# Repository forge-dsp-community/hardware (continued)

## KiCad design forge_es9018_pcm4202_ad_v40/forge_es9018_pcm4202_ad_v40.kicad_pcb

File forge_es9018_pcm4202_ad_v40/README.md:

# Forge ES9018/PCM4202 AD/DA V4.0 – KiCad-Rekonstruktion

> **Unfertiger Zwischenstand, nicht poliert.** Die Rekonstruktion stammt aus 300-dpi-Bildern und ist nicht gegen eine echte Platine geprüft. Es fehlen noch 6 Verbindungen, viele Bauteilwerte sind unbekannt, die Bauteilnamen sind neu vergeben und der DRC meldet Kosmetik (Details unten). Nicht zum Fertigen verwenden.

| Unterseite (Bauteile) | Oberseite |
|---|---|
|  |  |

3D-Renderings aus KiCad (`kicad-cli pcb render --rotate '-35,0,±30' --zoom 0.9 --background opaque`).

Quelle: `forge/pcbs/ad_da/eln_ad_da/V40` (bitbucket.org/forge-dsp/pcbs, Mark Duprau,
Lizenz CC BY-NC-SA 4.0). Diese Rekonstruktion steht unter derselben Lizenz.

Das ist die **zentrale AD/DA-Trägerplatine** der Forge DSP 96ELN / ETON CORED8 (V40):
3× PCM4202 (ADC), 1× ES9018 (8-Kanal-DAC), PCA9554 (I²C-Expander). Die analogen
I/V-Ausgangsplatinen (`output/eln/V30`, `output/eln-3/…`) werden in die 4 Steckplätze
J1–J4 gesteckt, die Eingangsplatinen in die 6 Schlitze an der Oberkante.

## Dateien

| Datei | Inhalt |
|---|---|
| `forge_es9018_pcm4202_ad_v40.kicad_pro/.kicad_sch/.kicad_pcb` | KiCad-10-Projekt |
| `forge_ad_da.kicad_sym` | Projekt-Symbole (PCM4202, ES9018, PCA9554, generische) |
| `forge_ad_da.pretty/` | 48 Footprints, Padgeometrie aus den Originaldaten vermessen |
| `rekonstruktion/` | Python-Skripte + `model.json` (Bauteile, Pads, Netze) |

## Ausgangsdaten

Im Repo gibt es **keine echten Gerber/Eagle-Dateien**, nur:

* Eagle-Renderings je Lage (`TOP`, `ROUTE2`, `ROUTE3`, `BOTTOM`, `PADS`, `VIAS`, `HOLES`, `TPLACE`, `BPLACE`, `MILLING`), 300 dpi
* `ES9018-PCM4202_AD.pdf` von Eurocircuits: 4er-Nutzen, Kupferlagen als 300-dpi-Bilder aus den echten Gerbern, Bohrplan mit Bohrtabelle
* das Schaltplanbild `…-SCHEMA.png` (Bus-Darstellung, Netznamen am Bus nicht sichtbar)

## Vorgehen

1. Die Eurocircuits-Bilder werden per Kreuzkorrelation auf die Eagle-Renderings registriert (gedreht um 90°, ±1 px).
2. Kupfer zählt nur dort, wo **beide** Quellen Kupfer zeigen (Eagle um 1 px aufgeweitet). Jede Quelle hat bei 300 dpi eigene 1-px-Brücken; die UND-Verknüpfung entfernt sie.
3. Netze ergeben sich aus den Kupfer-Inseln pro Lage, verbunden über Vias und Durchsteckpads.
4. Pads kommen aus den Lötstopp-Öffnungen (PCB-View Top/Bottom); die ICs werden über Pinraster plus Netzplausibilität eingepasst.
5. Konsistenzprüfung gegen den Original-Schaltplan (`validate.py`, `cmp.py`). Bestätigt sind z. B.:
   * PCM4202: S/M→3V3, FMT0/1→GND, FS0/FS1/HPFD/MCLK/LRCLK/BCLK gemeinsam, SDOUT je Chip getrennt
   * PCA9554 IO0…IO5 = CLIPL.3, CLIPR.3, CLIPL.2, CLIPR.2, CLIPL.1, CLIPR.1, IO6 = nRST.PCM4202, IO7 = RST.ES9018 (genau wie im Original)
   * J1…J4: I.2+, I.2−VREF, I.2−, I.1+, I.1−VREF, I.1− = VOUT2/1 … VOUT8/7 des ES9018
   * X100 Pin 3…16 wie im Original (SDA/SCL.PIPE, AD.OUT.1…3, LOCK, MCLK, BCLK.IN/OUT, LRCLK)
6. Die Bohrungen stimmen 1:1 mit der Eurocircuits-Bohrtabelle überein: Vias 0,25/0,30/0,40/0,50/0,60/0,80 mm, 20× 0,7 mm Halbloch-Kontakte, 4× 1,0 mm, 3× 2,0 mm.

## Ergebnis

* **Platine:** 53,21 × 56,39 mm, 4 Lagen. Umriss mit Schlitzen aus der Fräslage.
  Kupfer auf F/In1/In2/B als **3759 Leiterbahn-Segmente** und **174 Flächen-Zonen** mit Netz (siehe „Kupfer: Leiterbahnen statt Zonen“), dazu 332 Vias, 3 Montagebohrungen und der Bestückungsdruck oben/unten als Grafik.
  Fast alle Bauteile sitzen auf der **Unterseite**.
* **Schaltplan:** 97 Symbole, 103 Netze, Bauteilgruppen verdrahtet, globale Labels nur zwischen Gruppen (siehe Schaltplan). Schaltplan und Platine sind verknüpft; der DRC mit Schaltplan-Abgleich ist fehlerfrei.
* **DRC** (`kicad-cli pcb drc --refill-zones --schematic-parity`): 0 Kurzschlüsse, 0 Clearance-Fehler, **6 offene Verbindungen** (siehe unten), genau wie in der Zonen-Fassung. Der Rest ist kosmetisch und war vorher schon da: 67 × Kupfer am Halbloch-/Platinenrand (Pads und Vias des Randkontakts), 13 Courtyard-Überlappungen, 1 THT-Pad im Courtyard, Druck über Kupfer.
  Neu sind nur Warnungen:
  * 69 × „Leiterbahn mit offenem Ende“, überwiegend Sackgassen im Originalkupfer.
  * 9 × „Via nur einlagig angebunden“: Diese Vias haben auf den übrigen Lagen nur ihren eigenen Ring als Kupfer (~1 mm). Als Zone zählte dieser Ring für KiCad als Verbindung, als Via-Pad nicht mehr; elektrisch ändert sich nichts.

### Kupfer: Leiterbahnen statt Zonen

Kupfer liegt als **Leiterbahnen** vor. Breite Flächen (im Original Eagle-Polygone, auch Via-Felder) sind **Zonen mit Netz**, die KiCad selbst füllt (Clearance 0,08 mm, Thermals an THT-Pads).

Erzeugt mit `rekonstruktion/tracks.py` aus `polys.json`:

* Jede Kupferinsel wird mit 25 px/mm gerastert. Flächen werden über den Distanz-Transform erkannt (morphologisches Öffnen), der Rest wird skelettiert (Zhang-Suen), in Pfade zwischen End- und Knotenpunkten zerlegt, mit Douglas-Peucker vereinfacht, kurze Sporne fallen weg.
* Spurbreite = 2 × Distanz-Transform (Median), abgerundet auf Eagle-Breiten (0,1524 … 1,016 mm) und zusätzlich so begrenzt, dass Clearance zu fremdem Kupfer und Randabstand passen. Über das eigene Kupfer hinaus darf eine Spur höchstens bis zur Hälfte der Lücke zum Nachbarn ragen.
* Endpunkte an Pads/Vias desselben Netzes rasten auf die Pad-/Via-Mitte ein, an Flächen werden sie 0,3 mm hinein verlängert.
* Fläche wird, was einschließlich Pads und Vias ≥ 1,2 mm breit ist, dazu angrenzendes Kupfer ab 0,9 mm Breite. Danach rastert das Skript die erzeugten Spuren und vergleicht sie mit dem Originalkupfer (Formprüfung): Bleibt ein dicker Bereich (≥ 0,3 mm dick, ≥ 0,15 mm²) unbedeckt, wird er mit 0,5 mm Umgebung zur Fläche und die Insel neu berechnet. So werden Via-Felder Flächen statt Haufen kurzer breiter Spuren.
* Die Montagelöcher H1–H3 sind voll an die Flächen angebunden (ohne Thermal): In den Ecken erreicht die Fläche sie nur von einer Seite, mit Thermal bliebe nur ein Steg.
* Die Bild-Pads sind oft größer als die Footprint-Pads, manche Vias liegen direkt am Pad. Was nach dem Skelett innerhalb einer Insel noch getrennt ist, verbindet das Skript deshalb über einen kürzesten Weg durch das Originalkupfer.
* Zum Schluss prüft das Skript mit dem KiCad-DRC und macht Spuren mit Clearance- oder Randfehlern schrittweise schmaler. Spuren, die schon 0,1 mm breit sind, schiebt es um das fehlende Stück vom Hindernis weg.
* Die frühere Zonen-Fassung liegt als `rekonstruktion/forge_es9018_pcm4202_ad_v40_zonen.kicad_pcb` bei. Neu erzeugen mit `/usr/bin/python3 rekonstruktion/tracks.py .`; das Skript liest immer die Zonen-Fassung.

### Offene Punkte (im Original vorhanden, im 300-dpi-Bild zu dünn)

In KiCad erscheinen sie als Luftlinie und müssen von Hand nachgezogen werden:
`AD.OUT.3`, `nRST.PCM4202`, `VINR+.1`, `VINR+.2`, `VINR+.3`, `VOUT4+`.

### Teile, die nicht im Original-Schaltplanbild stehen

| Ref | Gehäuse | Funktion (aus Netzen abgeleitet) |
|---|---|---|
| U201 | SOT-23-5 | LDO 5V0 → **1V2_AVCC** (VDD_L/R des ES9018), Eingang über C254 (Ferrit/R?) |
| U202 | SOT-89 | Regler 3V3.NOHF → **1V2_DVCC** (VDD1–3 des ES9018) |
| U203 | SOIC-8 | Regler für **3V3_AVCC_L / 3V3_AVCC_R** (Eingang von X102.3) |
| U204 | SOT-23 | unbekannt (X102.4, C251/C252/C247) |
| X102 | 1×04, 2,54 mm | Versorgungseingang der Analogregler |
| X101 | 1×04, 2,0 mm | DATA2…DATA5 des ES9018 (Datenkanäle) |

### Unsicherheiten

* **Referenzen:** Der Original-Bestückungsdruck hat keine Namen. IC101…IC105, R10/C35 usw. folgen dem Schaltplan, alle passiven Teile heißen neu **C2xx/R2xx**, Pads ohne erkennbares Bauteil **TPxx**.
* **Werte:** Werte stammen aus dem Original-Schaltplan, zugeordnet über die Funktion (VREF/VCC/VDD-Tantal 47 µF, Abblock 100 nF, Eingang 2,7 nF). Mit `?` markierte Werte sind unbekannt; aus den Bildern lässt sich nicht unterscheiden, ob ein Pad-Paar R, C oder Ferrit ist.
* **Eingangsschlitze (Oberkante):** Bei C207…C212, C259 und TP1…TP4 ist unklar, ob es Kondensatoren oder Lötkontakte der Eingangsplatinen sind. Die 100-pF-Kondensatoren aus dem Schaltplan sitzen vermutlich auf den Eingangsplatinen.
* **Bauteilanzahl:** 71 Footprints mit Pads (ohne Randkontakt, Steckplätze, Jumper, Padgruppen). Ein Teil davon ist auf realen Platinen wohl unbestückt; der V40e-Schaltplan markiert mehrere Kondensatoren als „n.c.“.
* **U.FL (X-MCLK-DA):** Nur der Signalpad (TP17, Netz `MCLK.DA` → ES9018 XI) ist sicher erkannt. Die Massepads liegen in der GND-Fläche.

## 3D-Modelle

* Alle Bauteile haben KiCad-eigene 3D-Modelle (STEP aus `${KICAD10_3DMODEL_DIR}`), eingetragen in `forge_ad_da.pretty` und in der Platine. Fast alles sitzt auf der Unterseite; die Bilder oben zeigen beide Seiten.
* Zuordnung: C_0603 (Pad-Abstand bis 2 mm) → `C_0603_1608Metric` (R201 → `R_0603_1608Metric`), C_0805 → `C_0805_2012Metric`, L_C_1206ish → `C_1206_3216Metric`, Tantal Case C → `CP_EIA-6032-28_Kemet-C`, SSOP-28 (PCM4202) → `SSOP-28_5.3x10.2mm_P0.65mm`, TQFP-64 (ES9018) → `TQFP-64_10x10mm_P0.5mm`, HVQFN-16 (PCA9554) → `WQFN-16-1EP_3x3mm_P0.5mm_EP1.6x1.6mm`, SOIC-8 → `SOIC-8_3.9x4.9mm_P1.27mm`, SOT-23 → `SOT-23`, SOT-23-5 → `SOT-23-5`, SOT-89 → `SOT-89-3`, X101 → `PinHeader_1x04_P2.00mm_Vertical`, X102 → `PinHeader_1x04_P2.54mm_Vertical`.
* C210, C211, C253 und C259 haben 0603-Pads, aber 3,6…4,7 mm Pad-Abstand. Ihr Modell richtet sich nach dem Abstand, damit der Körper auf den Pads liegt: `C_1206_3216Metric` bzw. `C_1812_4532Metric` für C259. Die echte Bauform ist unbekannt.
* U201 (SOT-23-5) und U203 (SOIC-8): Die Pin-Reihenfolge der rekonstruierten Footprints ist gespiegelt. Die Gehäuse sitzen richtig auf den Pads, die Pin-1-Markierung des Modells liegt aber am anderen Ende der Pin-1-Reihe. U204 (`SOT-23-3_custom`) passt nur ungefähr auf die Pads.
* Ohne Modell, weil Kupfer bzw. Bohrung der Platine selbst: Randkontakt X100, Steckplätze J1…J4 für die I/V-Platinen, Lötbrücken JP1…JP3, Bohrungen H1…H3. Die Pad-Gruppen TP1…TP18 haben kein Modell, weil das Bauteil (falls bestückt) unbekannt ist.
* Bilder: `kicad-cli pcb render --side bottom` bzw. `--side top` nach dem Füllen der Zonen.
* Neu setzen nach jedem Neuerzeugen von Bibliothek oder Platine (`pcb.py`, `tracks.py`): `/usr/bin/python3 rekonstruktion/models3d.py .`. Das Skript trägt die Modelle in die Bibliothek, die Platine und `rekonstruktion/<name>_zonen.kicad_pcb` ein.

## Schaltplan

`rekonstruktion/sch_layout.py` ordnet den aus `sch.py` erzeugten Schaltplan neu an (A2):

* Je IC ein Block: Die Kondensatoren eines Pins hängen an einer Drahtbahn direkt am Pin, gestaffelt nach außen, damit sich nichts kreuzt. Kondensatoren zwischen zwei Pins (VIN+/VIN−) stehen senkrecht dazwischen. Abblockkondensatoren hängen am Versorgungspin, an dem sie auf der Platine am nächsten sitzen (seitliche Pins über eine Bahn, Pins oben/unten per Draht).
* Globale Labels gibt es nur für Netze zwischen Blöcken (Takte, I²C, CLIP/Reset, VOUT → J1…J4, Randkontakt). Versorgung erscheint als Power-Symbole.
* Verdrahtete Netze tragen ihren Namen als lokales Label (`/NAME`). Die Netznamen der Platine sind daran angeglichen (`sch_layout.py <projekt> --pcb`). Der DRC mit Schaltplan-Abgleich ist ohne Abweichung.
* Die Netzliste ist geprüft identisch mit der Label-Fassung (`rekonstruktion/<name>_labels.kicad_sch`). Die ERC zeigt nur noch die 15 Warnungen zu Ein-Pin-Netzen, die es vorher auch gab.

## Neu erzeugen

`rekonstruktion/run_all.sh`, dann `polys.py`, `pcb.py <ordner> <name>` und `sch.py <ordner> <name>`, danach `/usr/bin/python3 rekonstruktion/sch_layout.py .` (Schaltplan anordnen). Das ergibt die Zonen-Fassung.
Dann `rekonstruktion/forge_es9018_pcm4202_ad_v40_zonen.kicad_pcb` löschen und `/usr/bin/python3 rekonstruktion/tracks.py .` ausführen (sichert die neue Zonen-Fassung und erzeugt die Leiterbahnen).
Danach `kicad-cli pcb drc --refill-zones --save-board --schematic-parity` ausführen.
Die Skripte lesen ihre Pfade aus Umgebungsvariablen: `FORGE_PCBS` (Checkout von forge-dsp/pcbs), `REK_TOOLS` (Ordner mit den Extraktionsskripten), `SDIR` (Arbeitsordner für Zwischenstände).

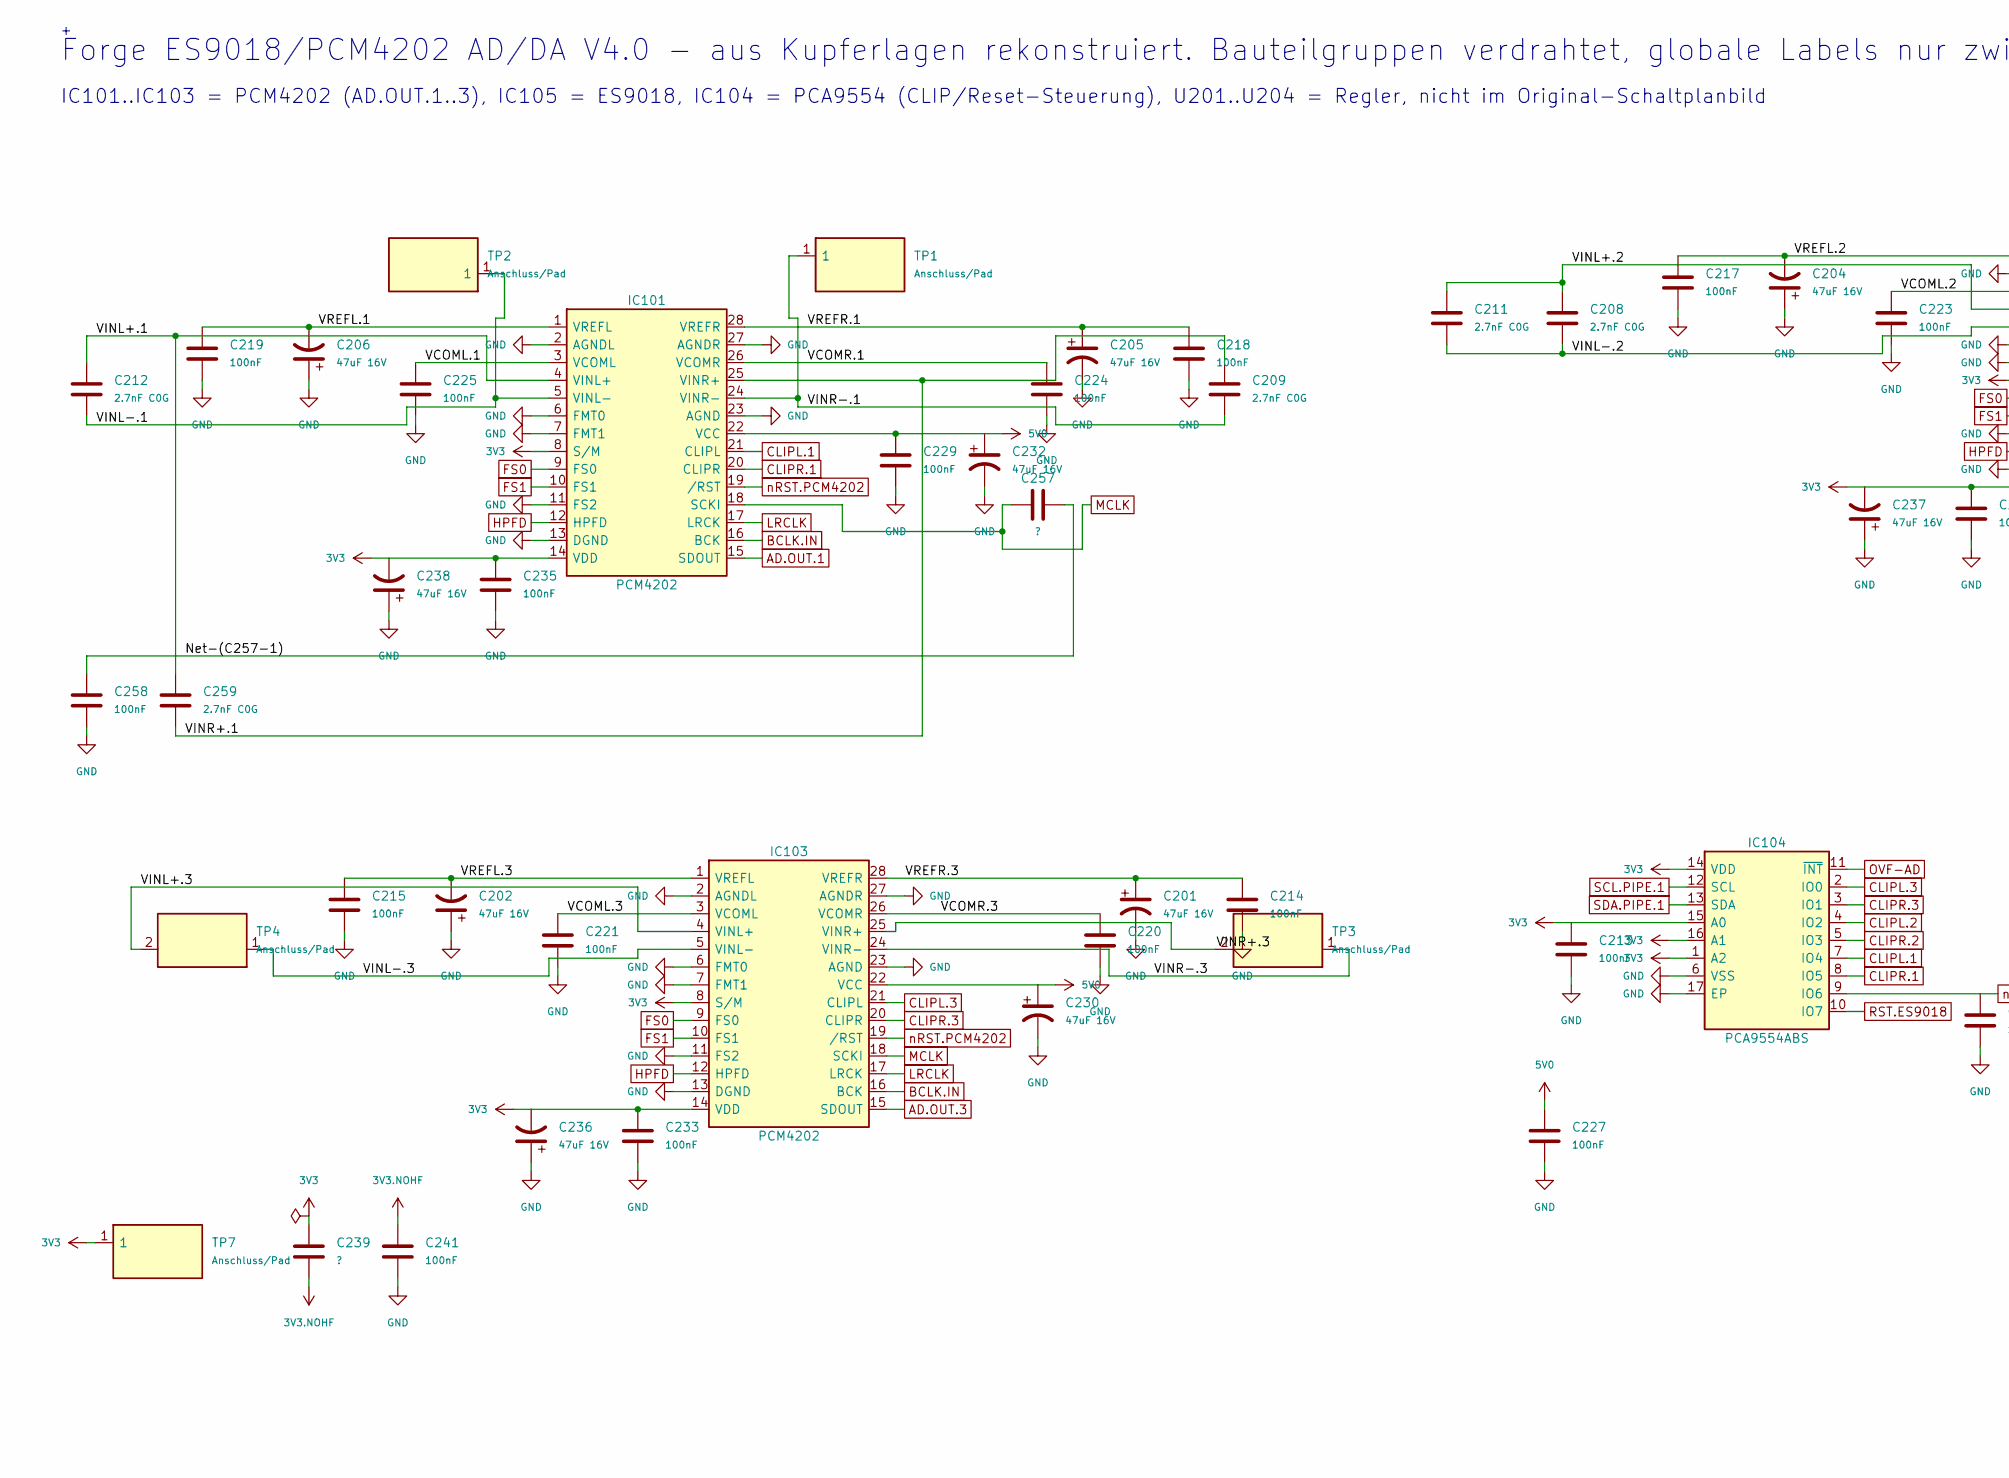
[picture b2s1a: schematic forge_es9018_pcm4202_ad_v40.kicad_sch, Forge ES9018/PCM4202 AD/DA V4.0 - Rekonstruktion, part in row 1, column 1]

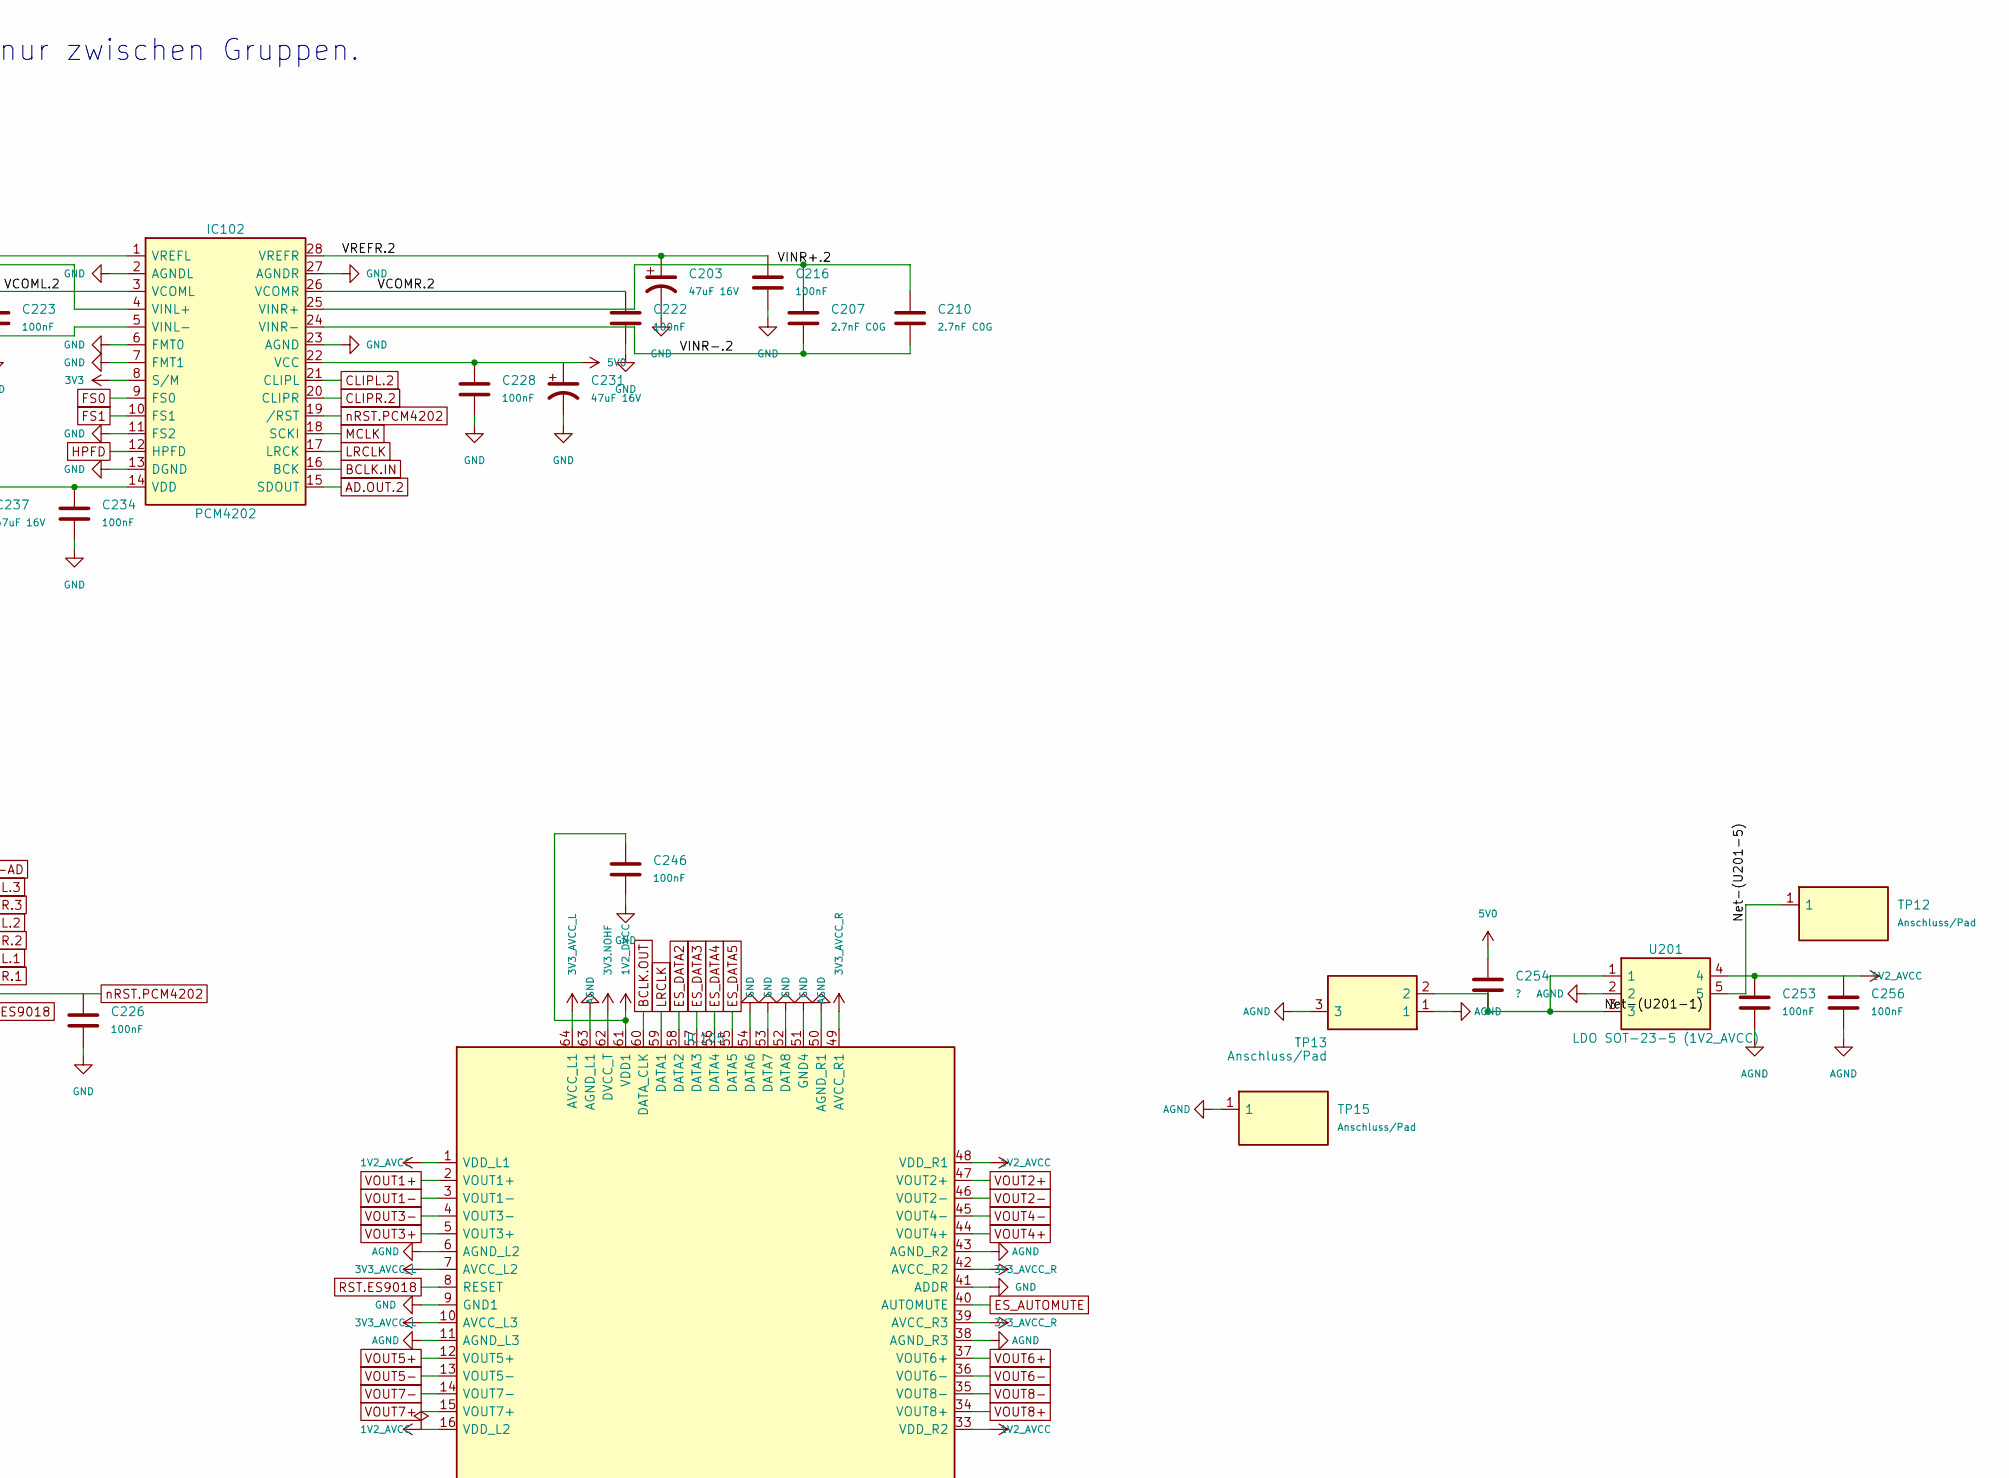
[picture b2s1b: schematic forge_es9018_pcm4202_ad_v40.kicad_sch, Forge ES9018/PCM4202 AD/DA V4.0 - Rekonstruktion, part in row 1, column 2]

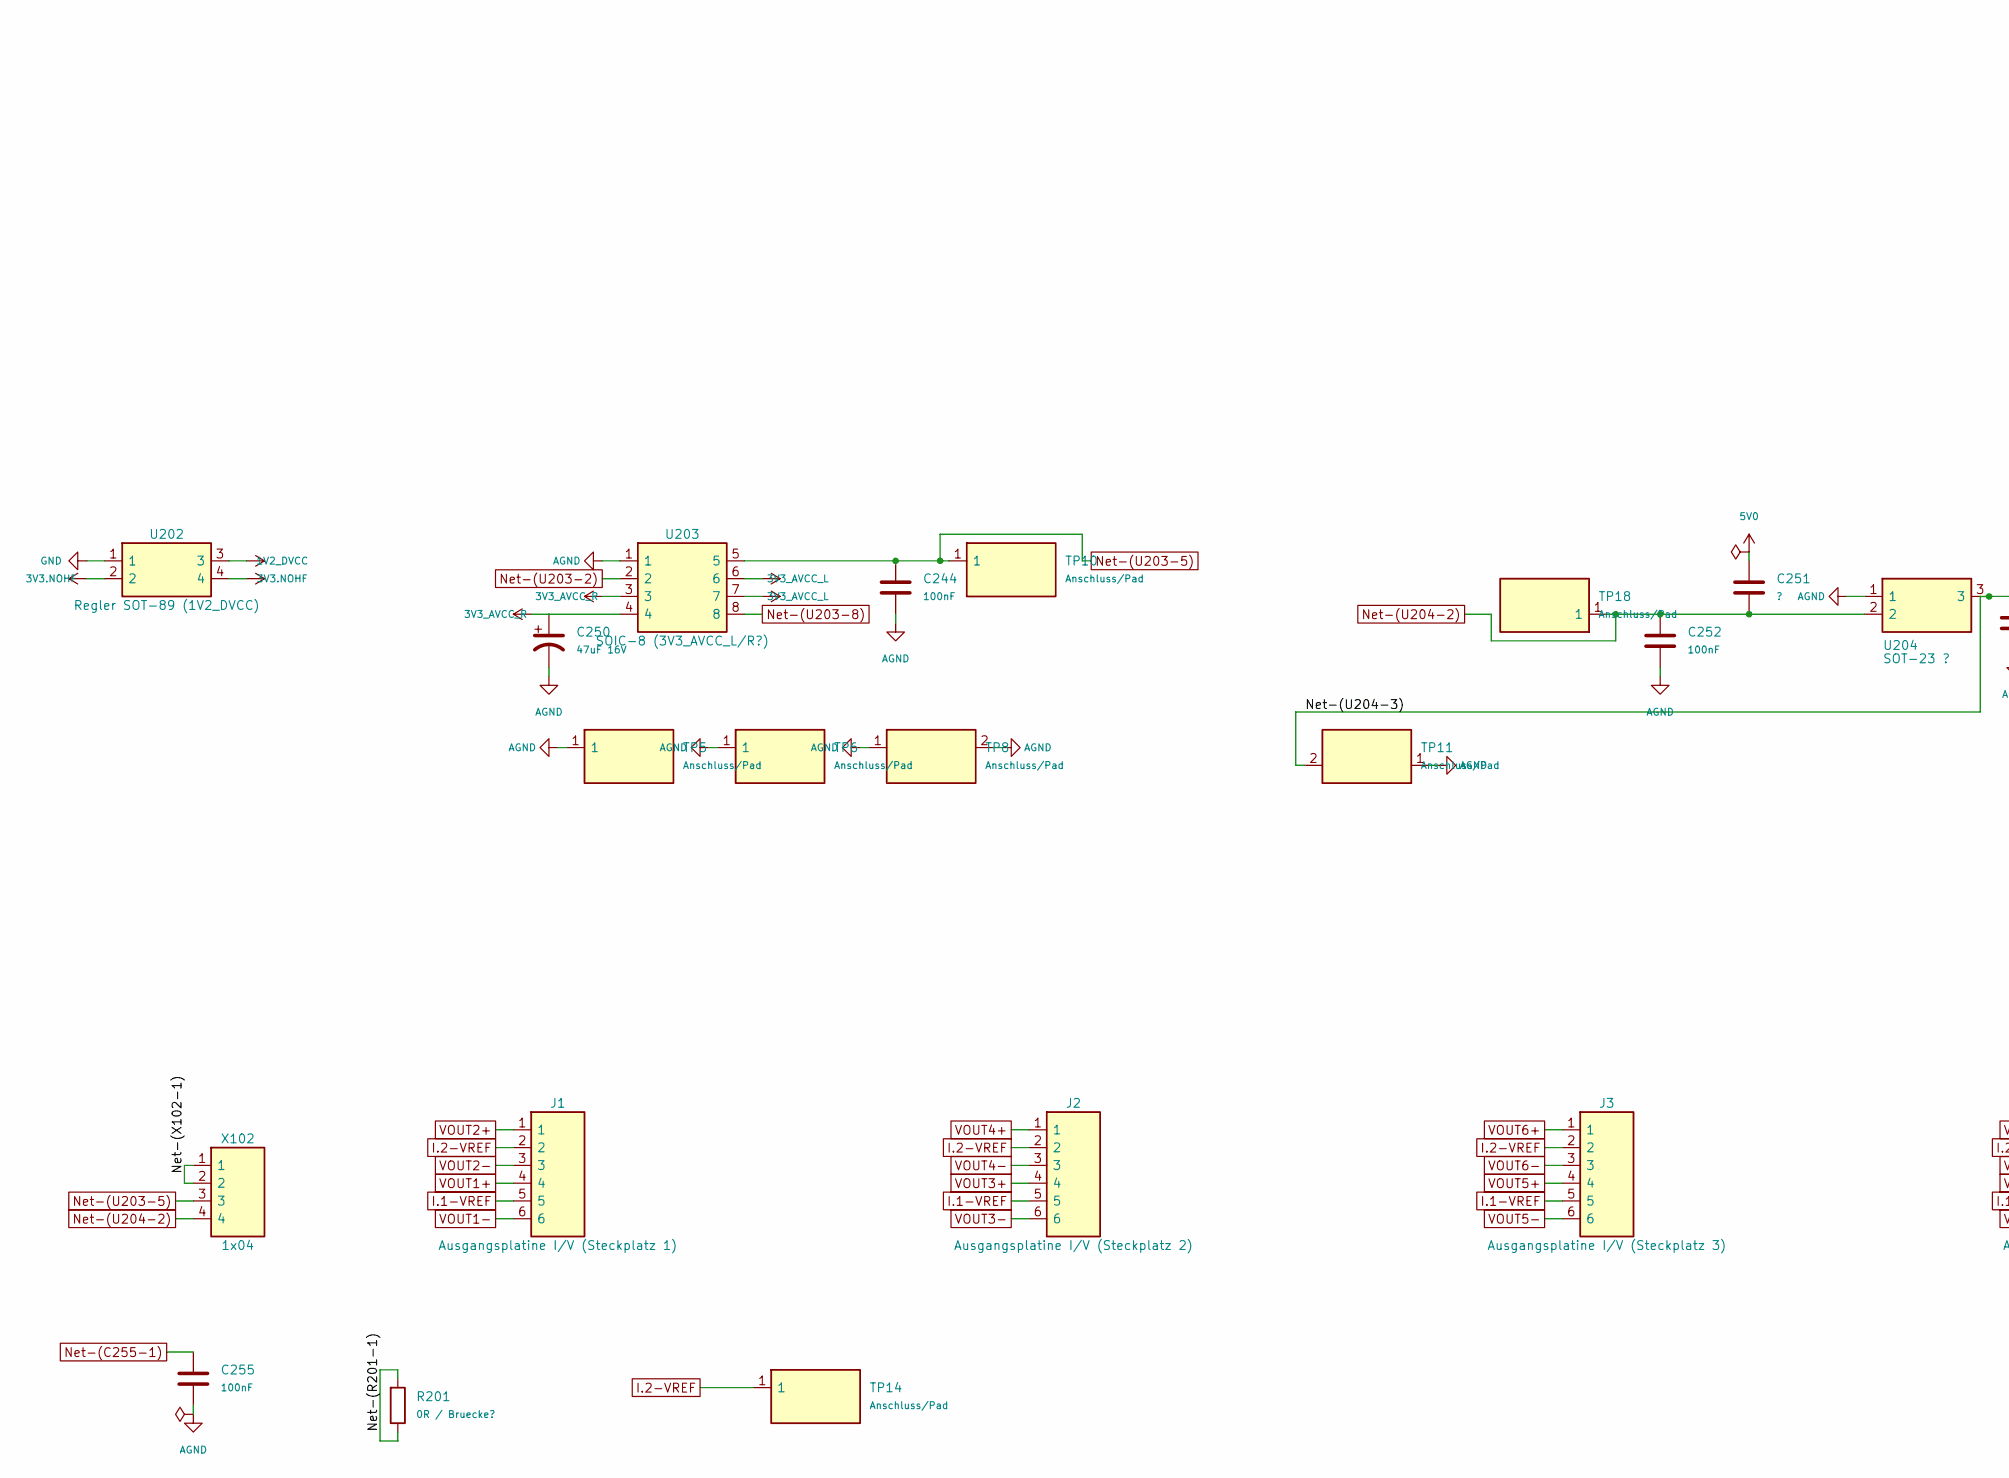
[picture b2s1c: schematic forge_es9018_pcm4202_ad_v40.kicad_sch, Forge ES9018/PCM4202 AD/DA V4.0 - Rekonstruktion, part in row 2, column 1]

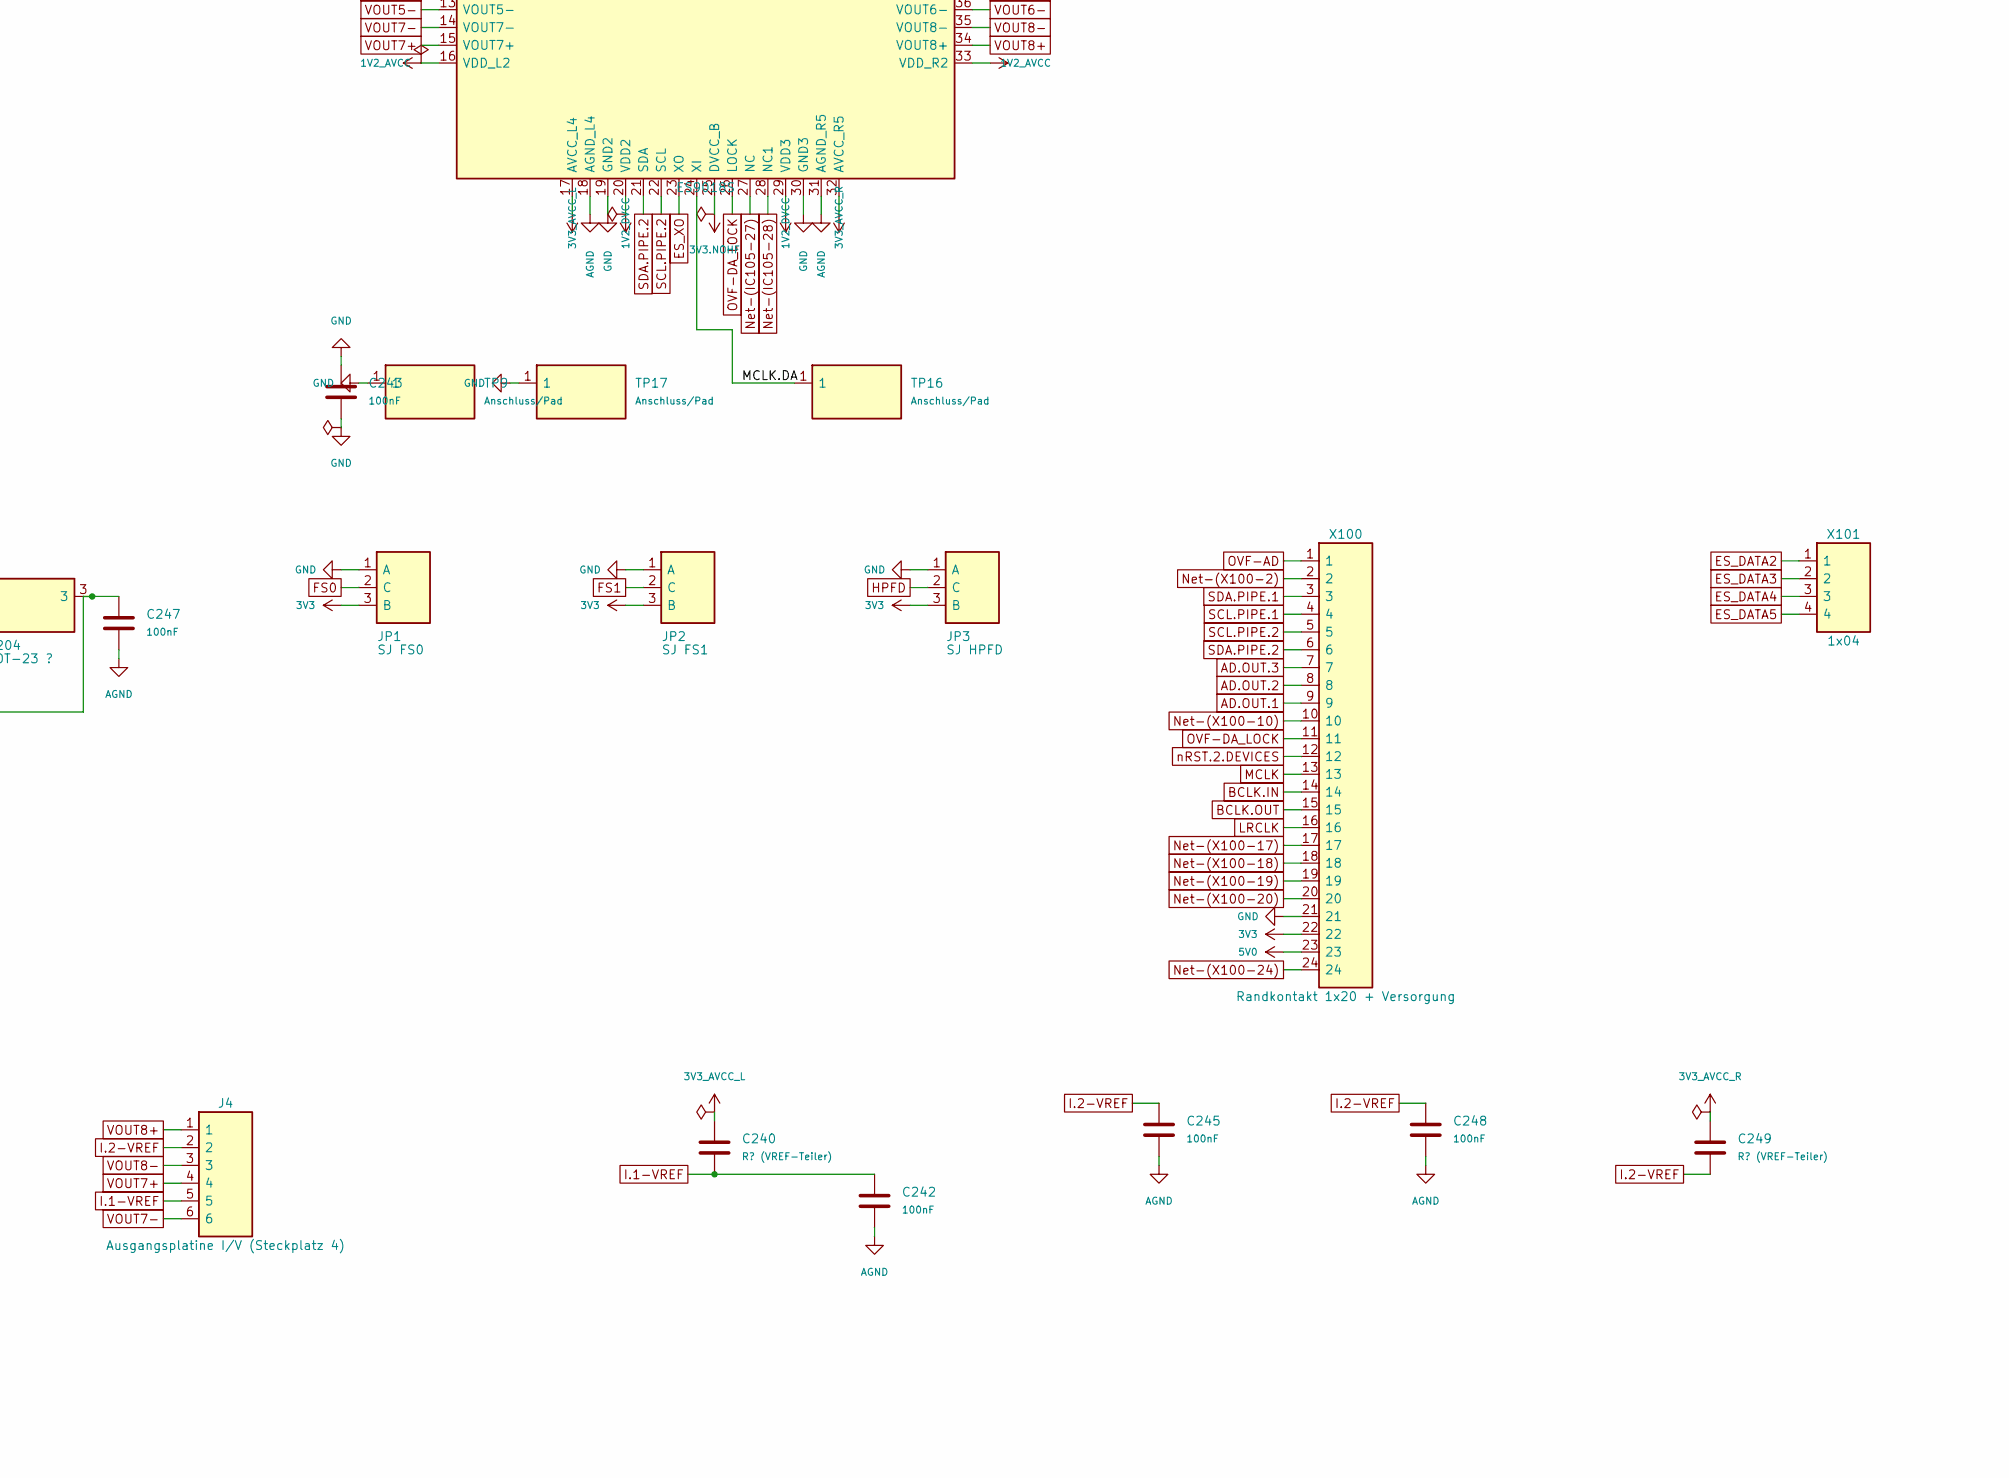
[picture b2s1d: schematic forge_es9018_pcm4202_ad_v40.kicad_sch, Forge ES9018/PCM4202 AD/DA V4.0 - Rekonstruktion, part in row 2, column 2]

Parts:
C201, C203, C205: 47uF 16V; CP_Tantalum_Case-C_TPSC_P4.90
C202, C204, C206: 47uF 16V; CP_Tantalum_Case-C_TPSC_P4.91
C207, C208, C209, C212: 2.7nF C0G; C_0603_Eagle_P1.69
C210, C211: 2.7nF C0G; C_0603_Eagle_P3.81
C213, C214, C216, C218, C220, C221, C222, C223, C224, C225, C227, C228, C229, C241: 100nF; C_0805_Eagle_P1.86
C215, C217, C219: 100nF; C_0805_Eagle_P1.87
C226, C247, C258: 100nF; C_0603_Eagle_P1.69
C230, C231, C232, C236, C237, C238, C250: 47uF 16V; CP_Tantalum_Case-C_TPSC_P5.00
C233, C234, C235, C252: 100nF; C_0805_Eagle_P1.95
C239: ?; C_0805_Eagle_P1.86
C240, C249: R? (VREF-Teiler); C_0603_Eagle_P1.70
C242: 100nF; L_C_1206ish_Eagle_P2.79
C243: 100nF; C_0603_Eagle_P1.87
C244, C248, C255: 100nF; C_0603_Eagle_P1.70
C245: 100nF; L_C_1206ish_Eagle_P2.80
C246: 100nF; C_0603_Eagle_P1.77
C251, C254: ?; C_0805_Eagle_P1.95
C253: 100nF; C_0603_Eagle_P3.56
C256: 100nF; C_0603_Eagle_P1.78
C257: ?; C_0603_Eagle_P1.69
C259: 2.7nF C0G; C_0603_Eagle_P4.74
IC101, IC102, IC103: PCM4202; SSOP-28_PCM4202_Eagle
IC104: PCA9554ABS; HVQFN-16_3x3_P0.5_EP
IC105: ES9018S; TQFP-64_ES9018_Eagle
J1: Ausgangsplatine I/V (Steckplatz 1); Slot_IV-Ausgang_1x06_P1.27_Rand
J2: Ausgangsplatine I/V (Steckplatz 2); Slot_IV-Ausgang_1x06_P1.27_Rand
J3: Ausgangsplatine I/V (Steckplatz 3); Slot_IV-Ausgang_1x06_P1.27_Rand
J4: Ausgangsplatine I/V (Steckplatz 4); Slot_IV-Ausgang_1x06_P1.27_Rand
JP1: SJ FS0; SolderJumper-3_Top
JP2: SJ FS1; SolderJumper-3_Top
JP3: SJ HPFD; SolderJumper-3_Top
R201: 0R / Bruecke?; C_0603_Eagle_P2.03
TP1: Anschluss/Pad; Pads_TP1
TP2: Anschluss/Pad; Pads_TP2
TP3: Anschluss/Pad; Pads_TP3
TP4: Anschluss/Pad; Pads_TP4
TP5: Anschluss/Pad; Pads_TP5
TP6: Anschluss/Pad; Pads_TP6
TP7: Anschluss/Pad; Pads_TP7
TP8: Anschluss/Pad; Pads_TP8
TP9: Anschluss/Pad; Pads_TP9
TP10: Anschluss/Pad; Pads_TP10
TP11: Anschluss/Pad; Pads_TP11
TP12: Anschluss/Pad; Pads_TP12
TP13: Anschluss/Pad; Pads_TP13
TP14: Anschluss/Pad; Pads_TP14
TP15: Anschluss/Pad; Pads_TP15
TP16: Anschluss/Pad; Pads_TP16
TP17: Anschluss/Pad; Pads_TP17
TP18: Anschluss/Pad; Pads_TP18
U201: LDO SOT-23-5 (1V2_AVCC); SOT-23-5_Eagle
U202: Regler SOT-89 (1V2_DVCC); SOT-89-3_Eagle
U203: SOIC-8 (3V3_AVCC_L/R?); SOIC-8_Eagle
U204: SOT-23 ?; SOT-23-3_custom
X100: Randkontakt 1x20 + Versorgung; X100_Castellated_1x20_P2.0_Power
X101: 1x04; HDR_X101
X102: 1x04; HDR_X102

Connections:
1V2_AVCC: C253.2, C256.2, IC105.1 (VDD_L1), IC105.16 (VDD_L2), IC105.33 (VDD_R2), IC105.48 (VDD_R1), U201.4
1V2_DVCC: C246.2, IC105.20 (VDD2), IC105.29 (VDD3), IC105.61 (VDD1), U202.3
3V3: C213.2, C233.2, C234.2, C235.2, C236.2, C237.2, C238.2, C239.2, IC101.8 (S/M), IC101.14 (VDD), IC102.8 (S/M), IC102.14 (VDD), IC103.8 (S/M), IC103.14 (VDD), IC104.1 (A2), IC104.14 (VDD), IC104.15 (A0), IC104.16 (A1), JP1.3 (B), JP2.3 (B), JP3.3 (B), TP7.1, X100.22
3V3.NOHF: C239.1, C241.1, IC105.25 (DVCC_B), IC105.62 (DVCC_T), U202.2, U202.4
3V3_AVCC_L: C240.1, IC105.7 (AVCC_L2), IC105.10 (AVCC_L3), IC105.17 (AVCC_L4), IC105.64 (AVCC_L1), U203.6, U203.7
3V3_AVCC_R: C249.2, C250.1, IC105.32 (AVCC_R5), IC105.39 (AVCC_R3), IC105.42 (AVCC_R2), IC105.49 (AVCC_R1), U203.3, U203.4
5V0: C227.2, C228.2, C229.2, C230.1, C231.1, C232.1, C251.2, C254.1, IC101.22 (VCC), IC102.22 (VCC), IC103.22 (VCC), X100.23
/MCLK.DA: IC105.24 (XI), TP16.1
/Net-(C257-1): C257.1, C258.1
/Net-(R201-1): R201.1, R201.2
/Net-(U201-1): C254.2, TP13.2, U201.1, U201.3
/Net-(U201-5): TP12.1, U201.5
/Net-(U204-3): C247.1, TP11.2, U204.3
/Net-(X102-1): X102.1, X102.2
/VCOML.1: C225.2, IC101.3 (VCOML)
/VCOML.2: C223.2, IC102.3 (VCOML)
/VCOML.3: C221.2, IC103.3 (VCOML)
/VCOMR.1: C224.2, IC101.26 (VCOMR)
/VCOMR.2: C222.2, IC102.26 (VCOMR)
/VCOMR.3: C220.2, IC103.26 (VCOMR)
/VINL+.1: C212.1, C259.2, IC101.4 (VINL+)
/VINL+.2: C208.1, C211.1, IC102.4 (VINL+)
/VINL+.3: IC103.4 (VINL+), TP4.2
/VINL-.1: C212.2, IC101.5 (VINL-), TP2.1
/VINL-.2: C208.2, C211.2, IC102.5 (VINL-)
/VINL-.3: IC103.5 (VINL-), TP4.1
/VINR+.1: C209.1, C259.1, IC101.25 (VINR+)
/VINR+.2: C207.1, C210.1, IC102.25 (VINR+)
/VINR+.3: IC103.25 (VINR+), TP3.2
/VINR-.1: C209.2, IC101.24 (VINR-), TP1.1
/VINR-.2: C207.2, C210.2, IC102.24 (VINR-)
/VINR-.3: IC103.24 (VINR-), TP3.1
/VREFL.1: C206.2, C219.2, IC101.1 (VREFL)
/VREFL.2: C204.2, C217.2, IC102.1 (VREFL)
/VREFL.3: C202.2, C215.2, IC103.1 (VREFL)
/VREFR.1: C205.1, C218.1, IC101.28 (VREFR)
/VREFR.2: C203.1, C216.1, IC102.28 (VREFR)
/VREFR.3: C201.1, C214.1, IC103.28 (VREFR)
AD.OUT.1: IC101.15 (SDOUT), X100.9
AD.OUT.2: IC102.15 (SDOUT), X100.8
AD.OUT.3: IC103.15 (SDOUT), X100.7
AGND: C242.1, C244.1, C245.2, C247.2, C248.2, C250.2, C252.2, C253.1, C255.2, C256.1, IC105.6 (AGND_L2), IC105.11 (AGND_L3), IC105.18 (AGND_L4), IC105.31 (AGND_R5), IC105.38 (AGND_R3), IC105.43 (AGND_R2), IC105.50 (AGND_R1), IC105.63 (AGND_L1), TP5.1, TP6.1, TP8.1, TP8.2, TP11.1, TP13.1, TP13.3, TP15.1, U201.2, U203.1, U204.1; also elsewhere on the board
BCLK.IN: IC101.16 (BCK), IC102.16 (BCK), IC103.16 (BCK), X100.14
BCLK.OUT: IC105.60 (DATA_CLK), X100.15
CLIPL.1: IC101.21 (CLIPL), IC104.7 (IO4)
CLIPL.2: IC102.21 (CLIPL), IC104.4 (IO2)
CLIPL.3: IC103.21 (CLIPL), IC104.2 (IO0)
CLIPR.1: IC101.20 (CLIPR), IC104.8 (IO5)
CLIPR.2: IC102.20 (CLIPR), IC104.5 (IO3)
CLIPR.3: IC103.20 (CLIPR), IC104.3 (IO1)
ES_AUTOMUTE: IC105.40 (AUTOMUTE)
ES_DATA2: IC105.58 (DATA2), X101.1
ES_DATA3: IC105.57 (DATA3), X101.2
ES_DATA4: IC105.56 (DATA4), X101.3
ES_DATA5: IC105.55 (DATA5), X101.4
ES_XO: IC105.23 (XO)
FS0: IC101.9 (FS0), IC102.9 (FS0), IC103.9 (FS0), JP1.2 (C)
FS1: IC101.10 (FS1), IC102.10 (FS1), IC103.10 (FS1), JP2.2 (C)
GND: C201.2, C202.1, C203.2, C204.1, C205.2, C206.1, C213.1, C214.2, C215.1, C216.2, C217.1, C218.2, C219.1, C220.1, C221.1, C222.1, C223.1, C224.1, C225.1, C226.2, C227.1, C228.1, C229.1, C230.2, C231.2, C232.2, C233.1, C234.1, C235.1, C236.1, C237.1, C238.1, C241.2, C243.1, C243.2, C246.1, C258.2, IC101.2 (AGNDL), IC101.6 (FMT0), IC101.7 (FMT1), IC101.11 (FS2), IC101.13 (DGND), IC101.23 (AGND), IC101.27 (AGNDR), IC102.2 (AGNDL), IC102.6 (FMT0), IC102.7 (FMT1), IC102.11 (FS2), IC102.13 (DGND), IC102.23 (AGND), IC102.27 (AGNDR), IC103.2 (AGNDL), IC103.6 (FMT0), IC103.7 (FMT1), IC103.11 (FS2), IC103.13 (DGND), IC103.23 (AGND), IC103.27 (AGNDR), IC104.6 (VSS), IC104.17 (EP), IC105.9 (GND1), IC105.19 (GND2), IC105.30 (GND3), IC105.41 (ADDR), IC105.51 (GND4), IC105.52 (DATA8), IC105.53 (DATA7), IC105.54 (DATA6), JP1.1 (A), JP2.1 (A), JP3.1 (A), TP9.1, TP17.1, U202.1, X100.21; also elsewhere on the board
HPFD: IC101.12 (HPFD), IC102.12 (HPFD), IC103.12 (HPFD), JP3.2 (C)
I.1-VREF: C240.2, C242.2, J1.5, J2.5, J3.5, J4.5
I.2-VREF: C245.1, C248.1, C249.1, J1.2, J2.2, J3.2, J4.2, TP14.1
LRCLK: IC101.17 (LRCK), IC102.17 (LRCK), IC103.17 (LRCK), IC105.59 (DATA1), X100.16
MCLK: C257.2, IC101.18 (SCKI), IC102.18 (SCKI), IC103.18 (SCKI), X100.13
unnamed: C244.2, TP10.1, U203.5, X102.3
unnamed: C251.1, C252.1, TP18.1, U204.2, X102.4
OVF-AD: IC104.11 (~INT), X100.1
OVF-DA_LOCK: IC105.26 (LOCK), X100.11
RST.ES9018: IC104.10 (IO7), IC105.8 (RESET)
SCL.PIPE.1: IC104.12 (SCL), X100.4
SCL.PIPE.2: IC105.22 (SCL), X100.5
SDA.PIPE.1: IC104.13 (SDA), X100.3
SDA.PIPE.2: IC105.21 (SDA), X100.6
VOUT1+: IC105.2 (VOUT1+), J1.4
VOUT1-: IC105.3 (VOUT1-), J1.6
VOUT2+: IC105.47 (VOUT2+), J1.1
VOUT2-: IC105.46 (VOUT2-), J1.3
VOUT3+: IC105.5 (VOUT3+), J2.4
VOUT3-: IC105.4 (VOUT3-), J2.6
VOUT4+: IC105.44 (VOUT4+), J2.1
VOUT4-: IC105.45 (VOUT4-), J2.3
VOUT5+: IC105.12 (VOUT5+), J3.4
VOUT5-: IC105.13 (VOUT5-), J3.6
VOUT6+: IC105.37 (VOUT6+), J3.1
VOUT6-: IC105.36 (VOUT6-), J3.3
VOUT7+: IC105.15 (VOUT7+), J4.4
VOUT7-: IC105.14 (VOUT7-), J4.6
VOUT8+: IC105.34 (VOUT8+), J4.1
VOUT8-: IC105.35 (VOUT8-), J4.3
nRST.2.DEVICES: X100.12
nRST.PCM4202: C226.1, IC101.19 (/RST), IC102.19 (/RST), IC103.19 (/RST), IC104.9 (IO6)

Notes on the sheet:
Forge ES9018/PCM4202 AD/DA V4.0 - aus Kupferlagen rekonstruiert. Bauteilgruppen verdrahtet, globale Labels nur zwischen Gruppen.
IC101..IC103 = PCM4202 (AD.OUT.1..3), IC105 = ES9018, IC104 = PCA9554 (CLIP/Reset-Steuerung), U201..U204 = Regler, nicht im Original-Schaltplanbild

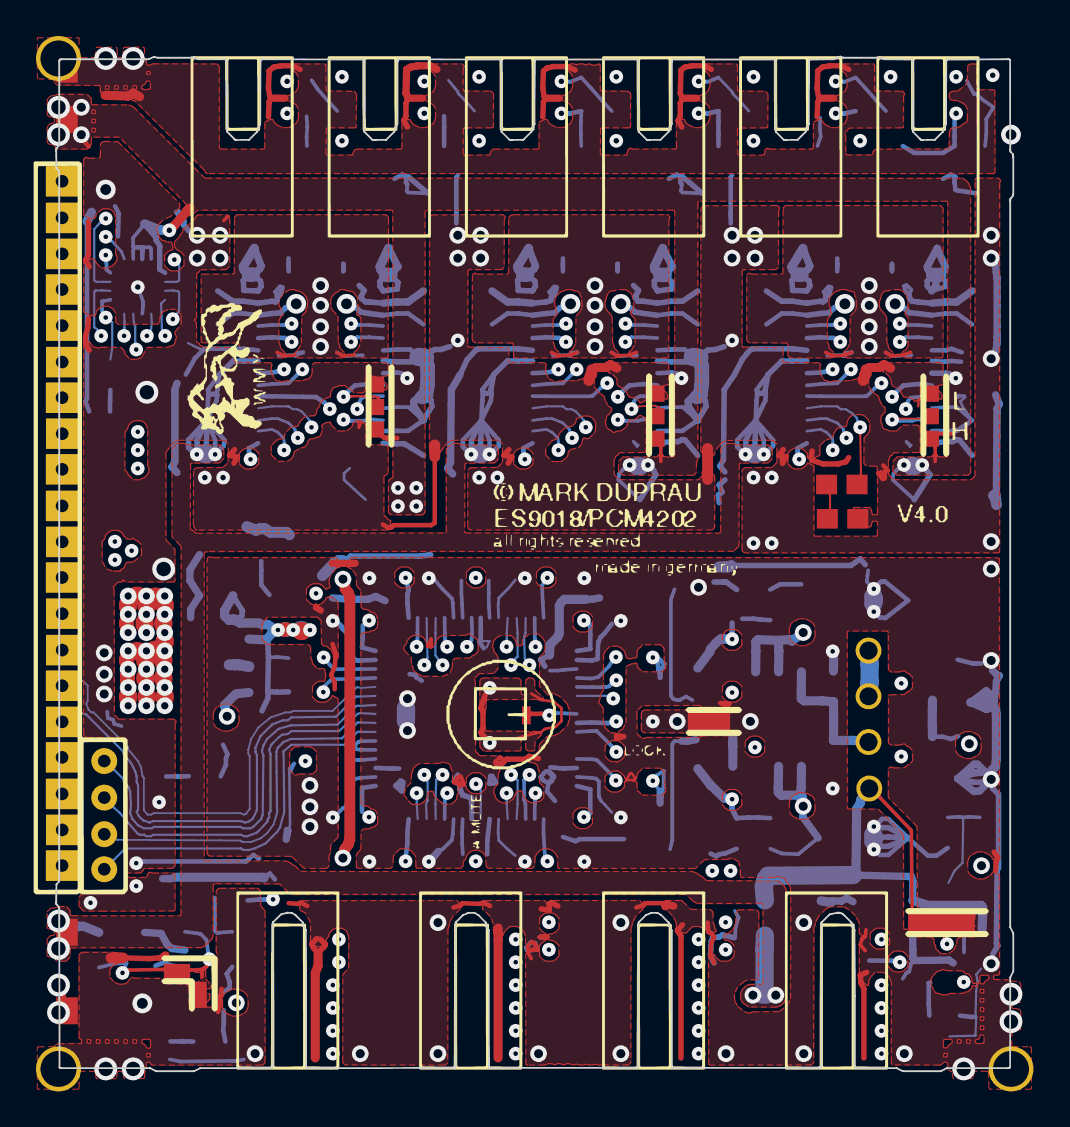
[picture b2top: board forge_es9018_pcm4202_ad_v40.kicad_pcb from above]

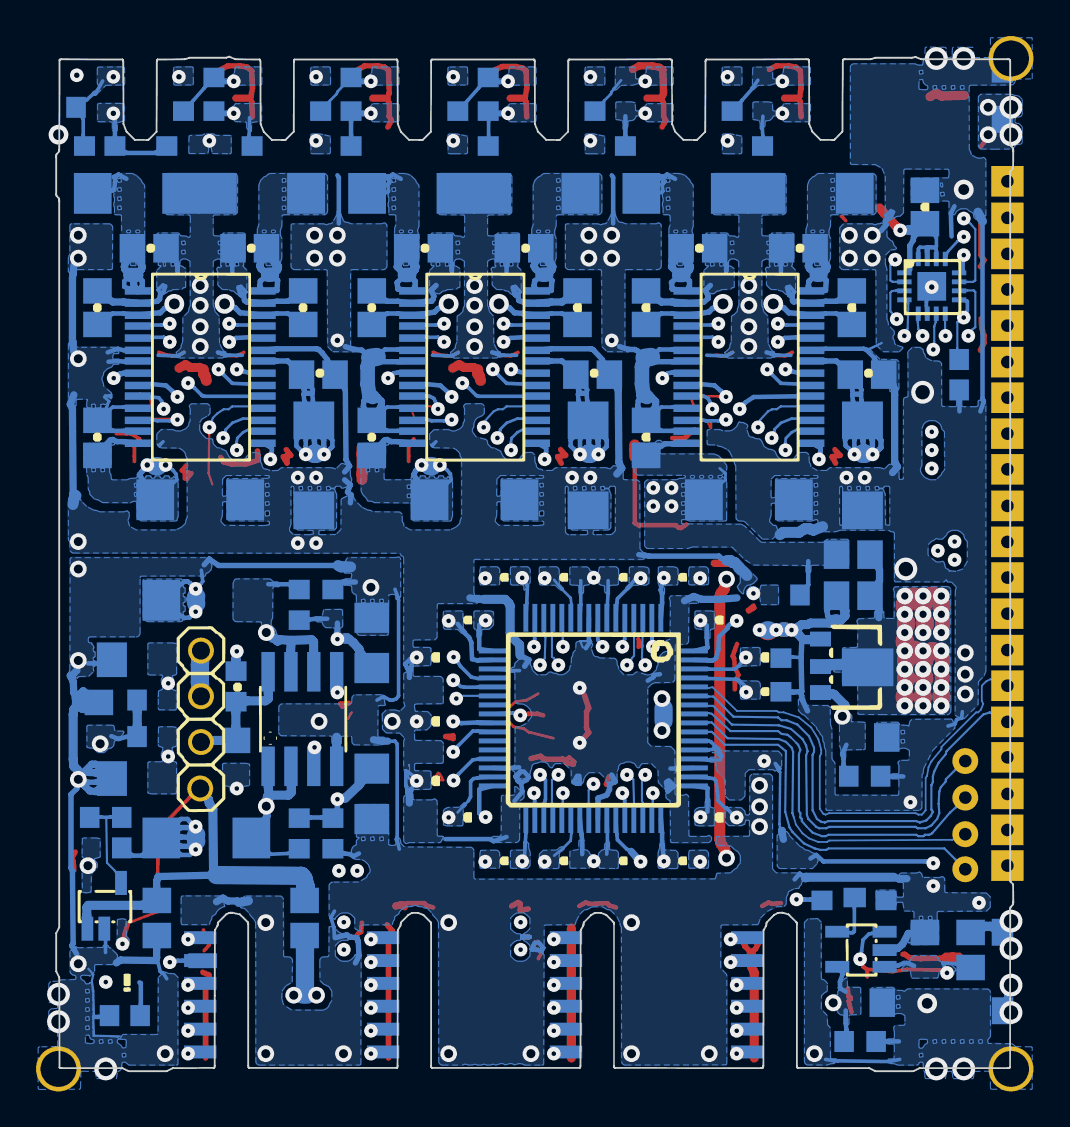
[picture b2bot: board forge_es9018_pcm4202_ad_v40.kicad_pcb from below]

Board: 4 copper layers, 53.2 x 56.4 mm, 100 parts (89 on the bottom side), 88 nets.

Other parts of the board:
H1, H2, H3: Bohrung 2.0; MountingHole_2.0mm_Pad2.5

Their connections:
AGND: H2.1, H3.1; also elsewhere on the board
GND: H1.1; also elsewhere on the board
